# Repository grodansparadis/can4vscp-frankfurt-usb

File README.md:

<h1>Frankfurt USB</h1>

Buffered and isolated interface for CAN4VSCP

Frankurt USB is a high speed USB interface to the CAN4VSCP bus. It is not available inte 
<a href="http://www.frogshop.se">FrogShop</a> at the moment but will probaly be available this year.

It is planed in two versions. One for DIN montage/wall mountage as the rest of the CAN4VSCP modules and
one version that is boxed.
<hr>

This project is part of the <a href="http://www.vscp.org">VSCP (Very Simple Control Protocol) project</a>. 

<hr>

This project is licensed under the 
<a href="http://creativecommons.org/licenses/by-nc-sa/3.0/">Creative Commons open source license Attribution-NonCommercial-ShareAlike 3.0 Unported</a>. 
Other license options are available by conacting <a href="malto:info@grodansparadis.com">Paradis of the Frog AB</a>

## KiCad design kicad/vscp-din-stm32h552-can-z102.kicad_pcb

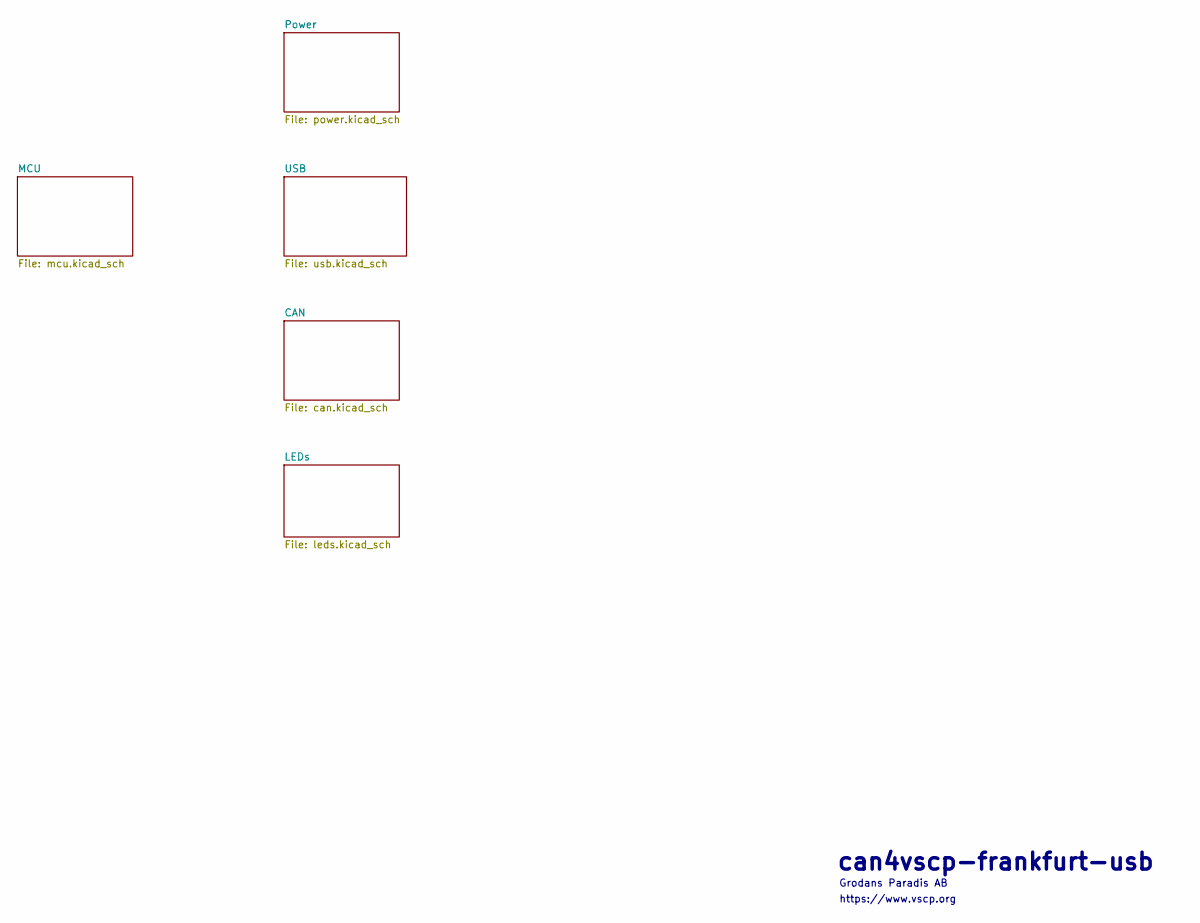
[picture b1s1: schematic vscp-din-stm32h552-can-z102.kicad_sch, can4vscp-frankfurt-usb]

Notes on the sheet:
https://www.vscp.org
can4vscp-frankfurt-usb
Grodans Paradis AB

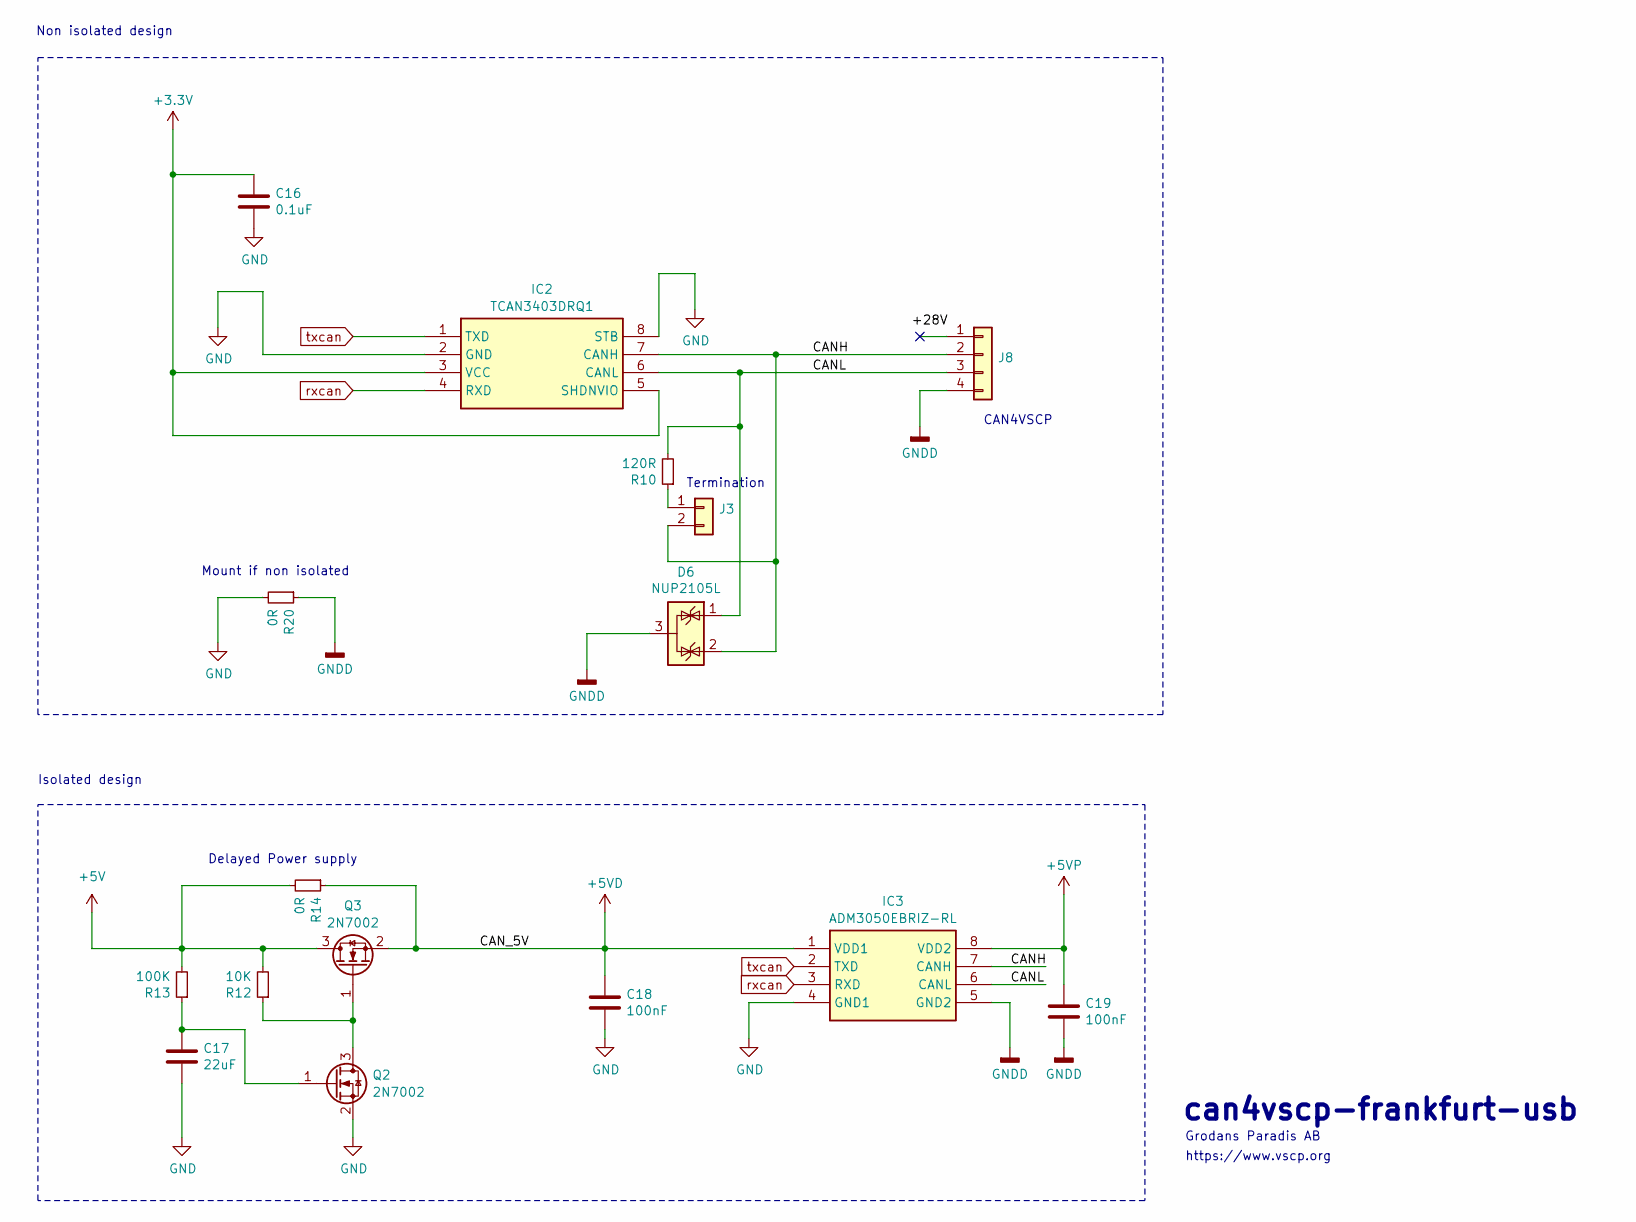
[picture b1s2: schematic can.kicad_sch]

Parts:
C16: 0.1uF; C_0805_2012Metric_Pad1.18x1.45mm_HandSolder
C17: 22uF; C_0805_2012Metric_Pad1.18x1.45mm_HandSolder
C18, C19: 100nF; C_0805_2012Metric_Pad1.18x1.45mm_HandSolder
D6: NUP2105L; SOT-23
IC2: TCAN3403DRQ1; SOIC127P600X175-8N; Mouser Part Number 595-TCAN3403DRQ1
IC3: ADM3050EBRIZ-RL; SOIC127P1031X265-8N; Mouser Part Number 584-ADM3050EBRIZ-RL
J3: Conn_01x02; PinHeader_1x02_P2.54mm_Vertical
J8: Conn_01x04; PhoenixContact_MC_1,5_4-G-3.81_1x04_P3.81mm_Horizontal
Q2, Q3: 2N7002; SOT-23
R10: 120R; R_0805_2012Metric_Pad1.20x1.40mm_HandSolder
R12: 10K; R_0805_2012Metric_Pad1.20x1.40mm_HandSolder
R13: 100K; R_0805_2012Metric_Pad1.20x1.40mm_HandSolder
R14, R20: 0R; R_0805_2012Metric_Pad1.20x1.40mm_HandSolder

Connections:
+3.3V: C16.1, IC2.3 (VCC), IC2.5 (SHDNVIO); also elsewhere on the board
+5V: Q3.3 (D), R12.2, R13.2, R14.2; also elsewhere on the board
+5VD: C18.1, IC3.1 (VDD1), Q3.2 (S), R14.1
+5VP: C19.1, IC3.8 (VDD2); also elsewhere on the board
/CAN/CANH: D6.2 (K), IC2.7 (CANH), IC3.7 (CANH), J3.2, J8.2
/CAN/CANL: D6.1 (K), IC2.6 (CANL), IC3.6 (CANL), J8.3, R10.2
GND: C16.2, C17.2, C18.2, IC2.2 (GND), IC2.8 (STB), IC3.4 (GND1), Q2.2 (S), R20.2; also elsewhere on the board
GNDD: C19.2, D6.3 (A), IC3.5 (GND2), J8.4, R20.1; also elsewhere on the board
unnamed: J3.1, R10.1
unnamed: Q2.3 (D), Q3.1 (G), R12.1
unnamed: C17.1, Q2.1 (G), R13.1
rxcan: IC2.4 (RXD), IC3.3 (RXD); also elsewhere on the board
txcan: IC2.1 (TXD), IC3.2 (TXD); also elsewhere on the board

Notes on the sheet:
Termination
CAN4VSCP
https://www.vscp.org
Delayed Power supply
Isolated design
Non isolated design
can4vscp-frankfurt-usb
Grodans Paradis AB
Mount if non isolated

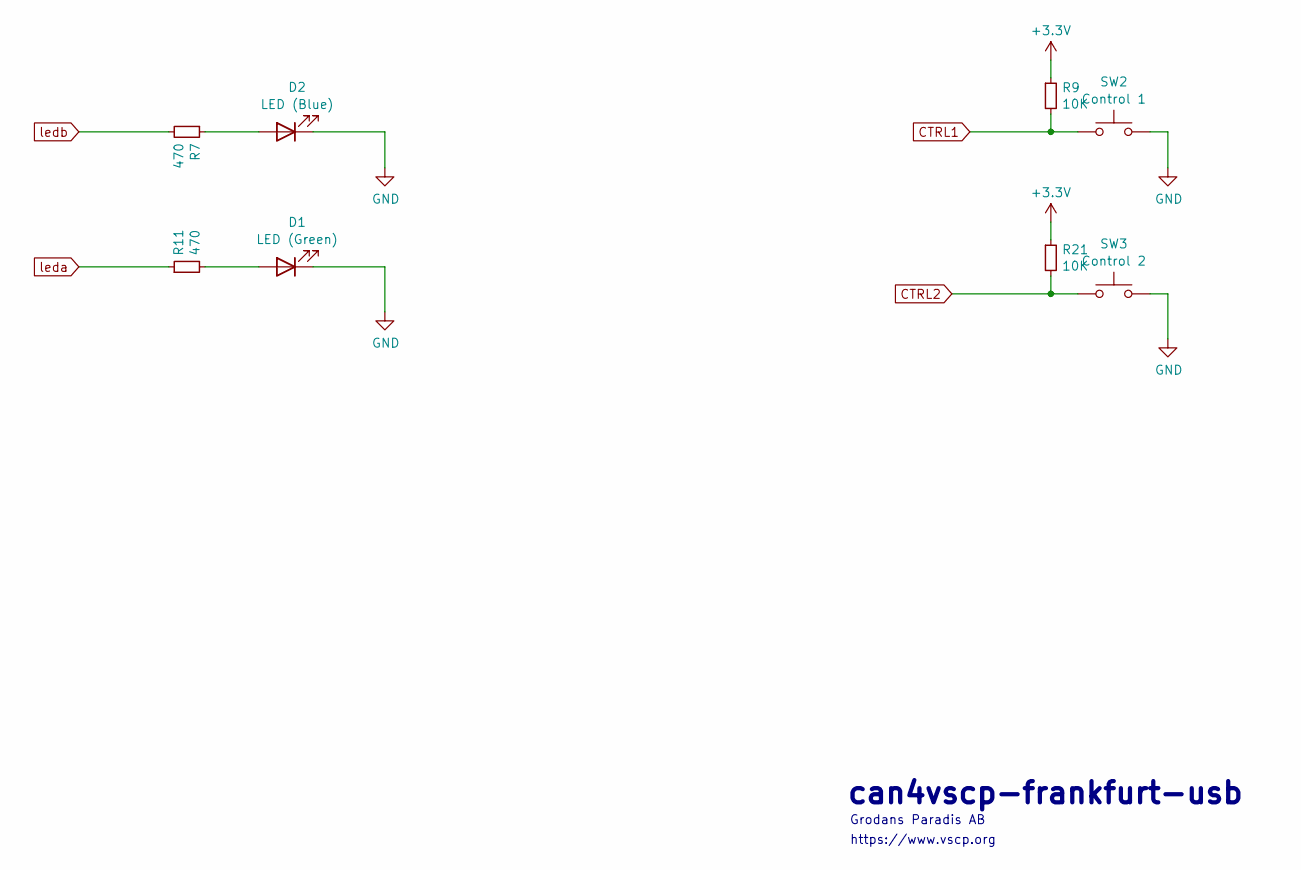
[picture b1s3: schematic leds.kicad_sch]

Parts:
D1: LED (Green); LED_0805_2012Metric
D2: LED (Blue); LED_0805_2012Metric
R7, R11: 470; R_0805_2012Metric
R9, R21: 10K; R_0805_2012Metric
SW2: Control 1; SW_SPST_Omron_B3FS-100xP
SW3: Control 2; SW_SPST_Omron_B3FS-100xP

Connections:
+3.3V: R9.1, R21.1; also elsewhere on the board
CTRL1: R9.2, SW2.1
CTRL2: R21.2, SW3.1
GND: D1.1 (K), D2.1 (K), SW2.2, SW3.2; also elsewhere on the board
unnamed: D1.2 (A), R11.2
unnamed: D2.2 (A), R7.1
leda: R11.1
ledb: R7.2

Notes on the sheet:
can4vscp-frankfurt-usb
https://www.vscp.org
Grodans Paradis AB

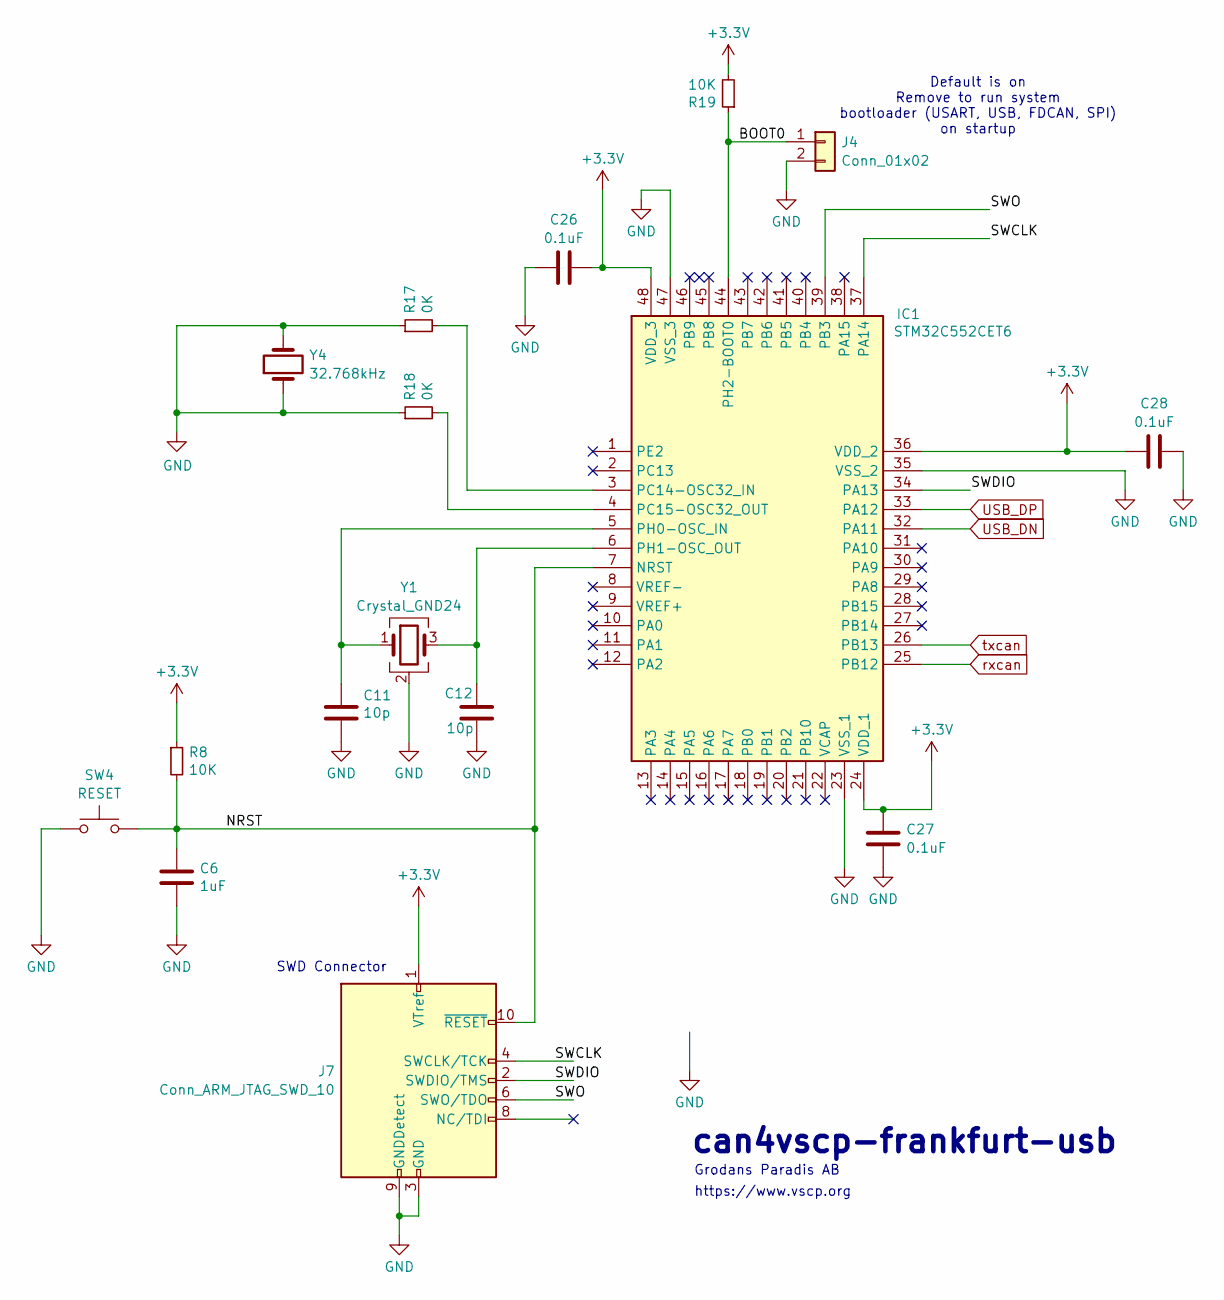
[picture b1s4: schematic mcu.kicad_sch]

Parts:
C6: 1uF; C_0805_2012Metric_Pad1.18x1.45mm_HandSolder
C11, C12: 10p; C_0805_2012Metric_Pad1.18x1.45mm_HandSolder
C26, C27, C28: 0.1uF; C_0805_2012Metric_Pad1.18x1.45mm_HandSolder
IC1: STM32C552CET6; QFP50P900X900X160-48N; Manufacturer_Part_Number STM32C552CET6
J4: Conn_01x02; PinHeader_1x02_P2.54mm_Vertical
J7: Conn_ARM_JTAG_SWD_10; PinHeader_2x05_P1.27mm_Vertical
R8: 10K; R_0805_2012Metric
R17, R18: 0K; R_0805_2012Metric_Pad1.20x1.40mm_HandSolder
R19: 10K; R_0805_2012Metric_Pad1.20x1.40mm_HandSolder
SW4: RESET; SW_SPST_Omron_B3FS-100xP
Y1: Crystal_GND24; Crystal_SMD_TXC_7M-4Pin_3.2x2.5mm_HandSoldering
Y4: 32.768kHz; Resonator-2Pin_W6.0mm_H3.0mm

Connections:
+3.3V: C26.2, C27.2, C28.1, IC1.24 (VDD_1), IC1.36 (VDD_2), IC1.48 (VDD_3), J7.1 (VTref), R8.1, R19.2; also elsewhere on the board
/MCU/BOOT0: IC1.44 (PH2-BOOT0), J4.1, R19.1
/MCU/NRST: C6.1, IC1.7 (NRST), J7.10 (~RESET), R8.2, SW4.2
/MCU/SWCLK: IC1.37 (PA14), J7.4 (SWCLK/TCK)
/MCU/SWDIO: IC1.34 (PA13), J7.2 (SWDIO/TMS)
/MCU/SWO: IC1.39 (PB3), J7.6 (SWO/TDO)
GND: C6.2, C11.2, C12.2, C26.1, C27.1, C28.2, IC1.23 (VSS_1), IC1.35 (VSS_2), IC1.47 (VSS_3), J4.2, J7.3 (GND), J7.5 (GND), J7.9 (GNDDetect), R17.1, R18.1, SW4.1, Y1.2 (G), Y1.4 (G), Y4.1, Y4.2; also elsewhere on the board
unnamed: IC1.3 (PC14-OSC32_IN), R17.2
unnamed: IC1.4 (PC15-OSC32_OUT), R18.2
unnamed: C11.1, IC1.5 (PH0-OSC_IN), Y1.1
unnamed: C12.1, IC1.6 (PH1-OSC_OUT), Y1.3
USB_DN: IC1.32 (PA11); also elsewhere on the board
USB_DP: IC1.33 (PA12); also elsewhere on the board
rxcan: IC1.25 (PB12); also elsewhere on the board
txcan: IC1.26 (PB13); also elsewhere on the board

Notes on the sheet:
https://www.vscp.org
SWD Connector
Default is on Remove to run system bootloader (USART, USB, FDCAN, SPI) on startup
Grodans Paradis AB
can4vscp-frankfurt-usb

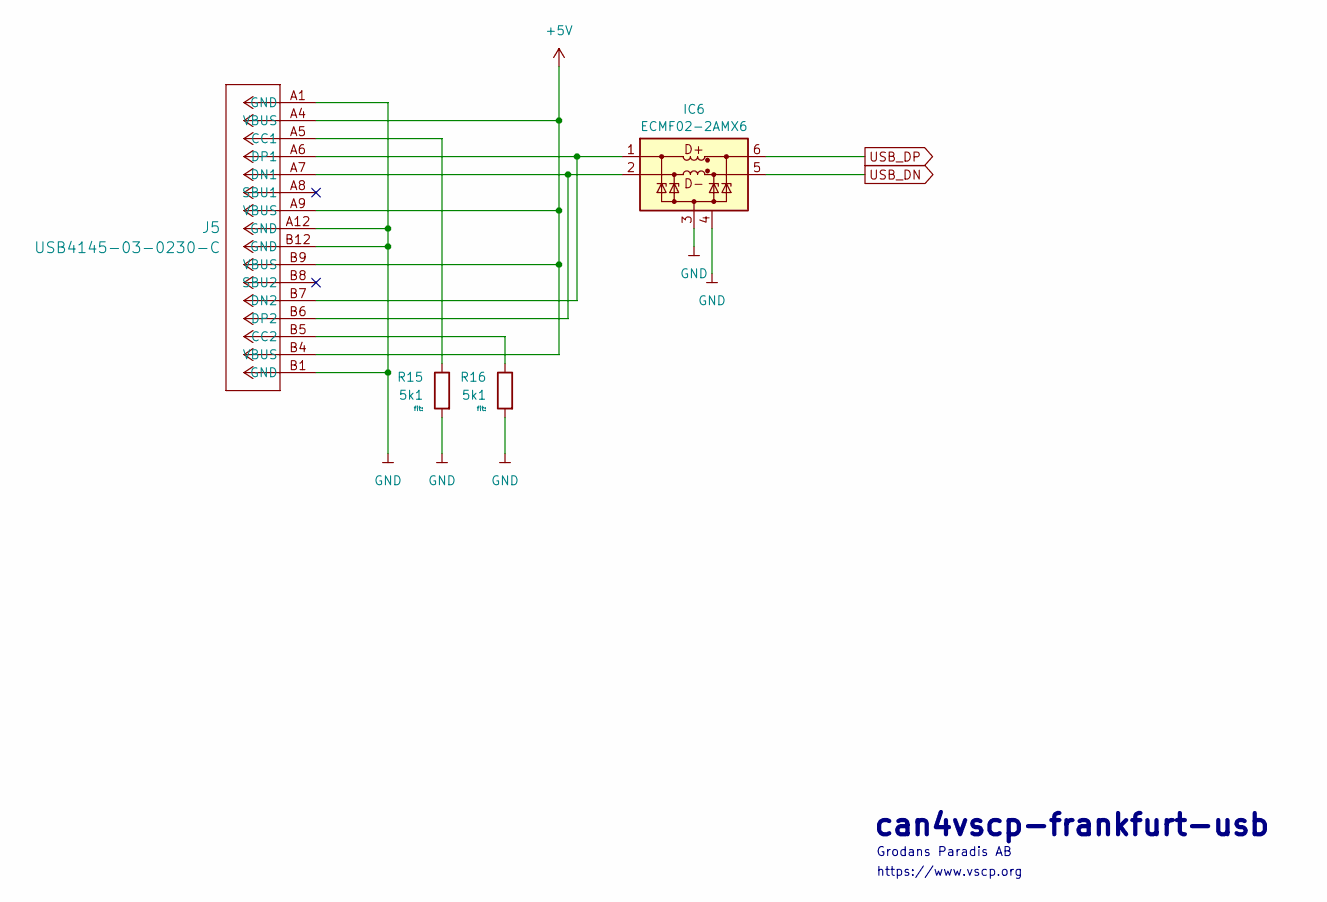
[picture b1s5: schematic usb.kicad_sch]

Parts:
IC6: ECMF02-2AMX6; ST_UQFN-6L_1.5x1.7mm_P0.5mm
J5: USB4145-03-0230-C; CONN_USB4145-03-0230-C_GCT
R15, R16: 5k1_0603_100mW_1%_E24_Chip-Resistor; R_0805_2012Metric; MPN any

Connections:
+5V: J5.A4 (VBUS), J5.A9 (VBUS), J5.B4 (VBUS), J5.B9 (VBUS); also elsewhere on the board
GND: IC6.3 (GND), IC6.4 (NC), J5.A1 (GND), J5.A12 (GND), J5.B1 (GND), J5.B12 (GND), R15.2, R16.2; also elsewhere on the board
unnamed: IC6.1 (D+_in), J5.A6 (DP1), J5.B7 (DN2)
unnamed: IC6.2 (D-_in), J5.A7 (DN1), J5.B6 (DP2)
unnamed: J5.A5 (CC1), R15.1
unnamed: J5.B5 (CC2), R16.1
USB_DN: IC6.5 (D-_out); also elsewhere on the board
USB_DP: IC6.6 (D+_out); also elsewhere on the board

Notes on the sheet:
https://www.vscp.org
Grodans Paradis AB
can4vscp-frankfurt-usb

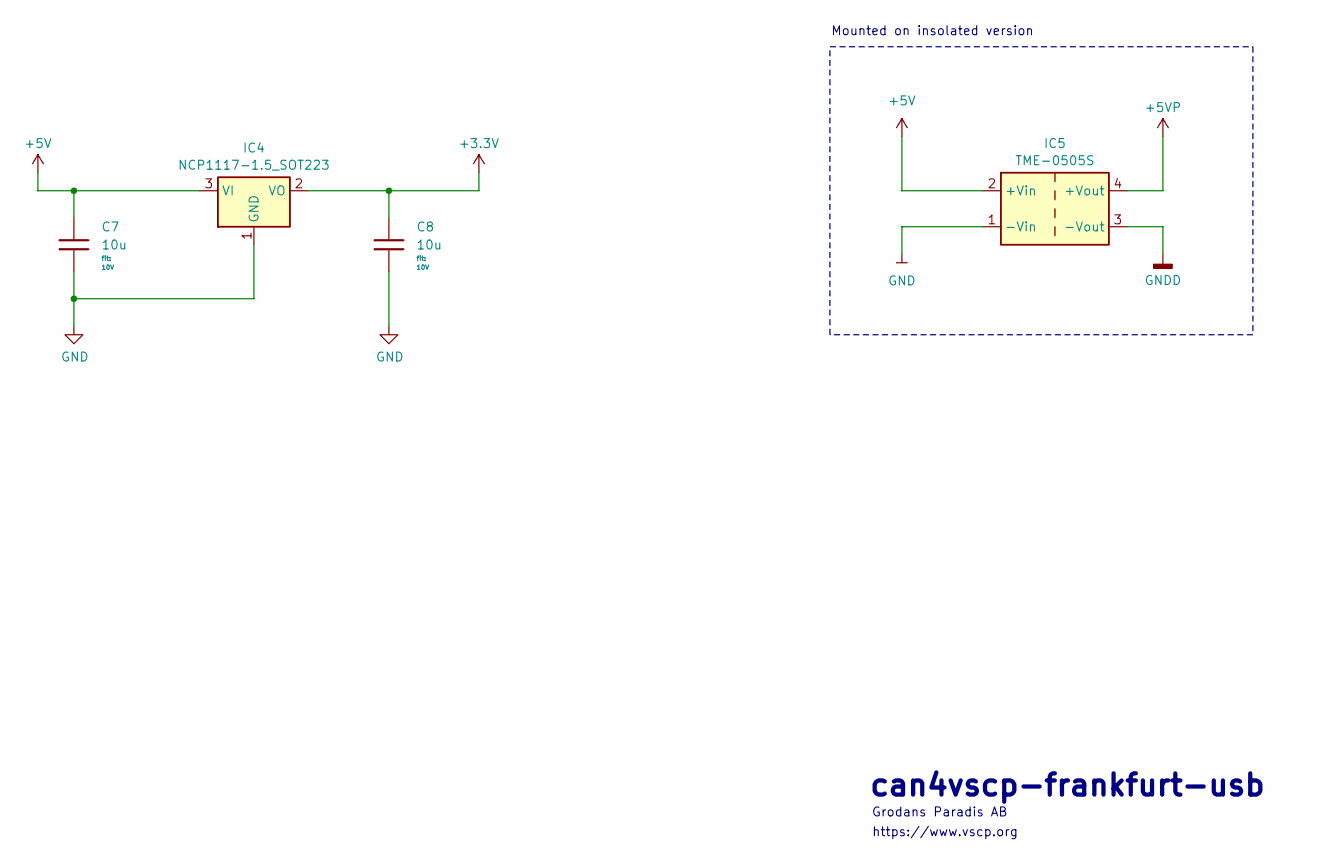
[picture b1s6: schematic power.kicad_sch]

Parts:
C7, C8: 10u_0805_X7R_10%_10V_-40C..125C_Chip-Capacitor; C_0805_2012Metric; MPN any
IC4: NCP1117-1.5_SOT223; SOT-223-3_TabPin2
IC5: TME-0505S; Converter_DCDC_TRACO_TME_03xxS_05xxS_12xxS_Single_THT

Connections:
+3.3V: C8.1, IC4.2 (VO); also elsewhere on the board
+5V: C7.1, IC4.3 (VI), IC5.2 (+Vin); also elsewhere on the board
+5VP: IC5.4 (+Vout); also elsewhere on the board
GND: C7.2, C8.2, IC4.1 (GND), IC5.1 (-Vin); also elsewhere on the board
GNDD: IC5.3 (-Vout); also elsewhere on the board

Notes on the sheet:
can4vscp-frankfurt-usb
Mounted on insolated version
https://www.vscp.org
Grodans Paradis AB

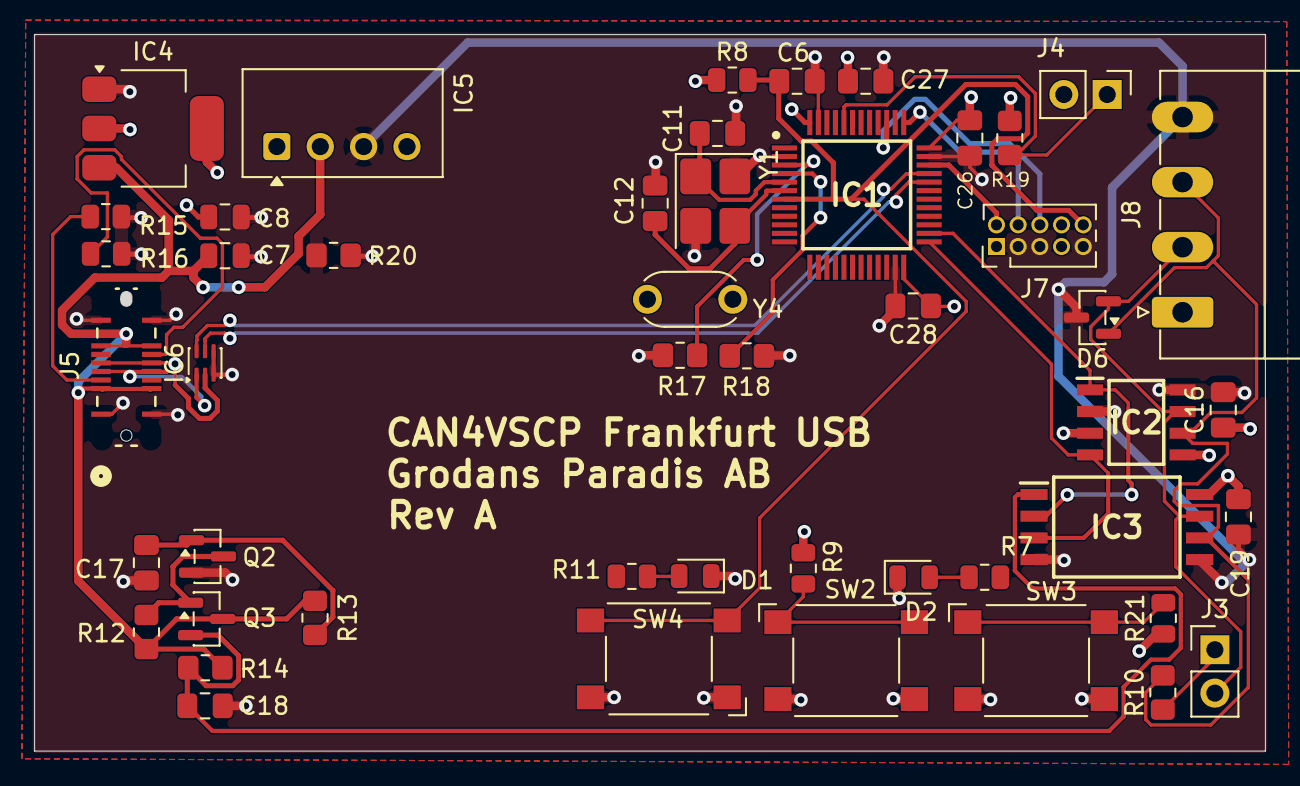
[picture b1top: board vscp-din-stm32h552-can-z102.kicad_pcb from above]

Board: 4 copper layers, 71.5 x 41.3 mm, 48 parts (0 on the bottom side), 32 nets.

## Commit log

2015-08-17 Initial checkin
2015-08-17 Ignoring work files
2015-08-17 updated initial info
2015-08-17 Changed license to Artistic License 3.0
2015-08-28 Removed junk
2015-11-03 Added boxed version and stepped to rev c
2015-11-03 Adding gerbers for the enclosure version
2015-12-03 Corrected processor type
2015-12-17 Updated readme and license
2023-03-07 rev c
2023-04-11 Removed Patreon as sponsor option
2025-09-30 /home/akhe/development/VSCP/can4vscp-odessa/LICENSE
2026-05-04 Added new STM32 based design
2026-05-04 Removed manual dirt
2026-05-04 Changed crystal to TXC 7V series
2026-05-04 Fixed power issue
2026-05-04 Added butons
2026-05-05 Updated license to CERN
2026-05-08 Reversion A schema and PCB
2026-05-08 Fixed 3D models
